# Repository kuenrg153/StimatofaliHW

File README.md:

# StimatofaliHW
Peer-to-Peer Energy

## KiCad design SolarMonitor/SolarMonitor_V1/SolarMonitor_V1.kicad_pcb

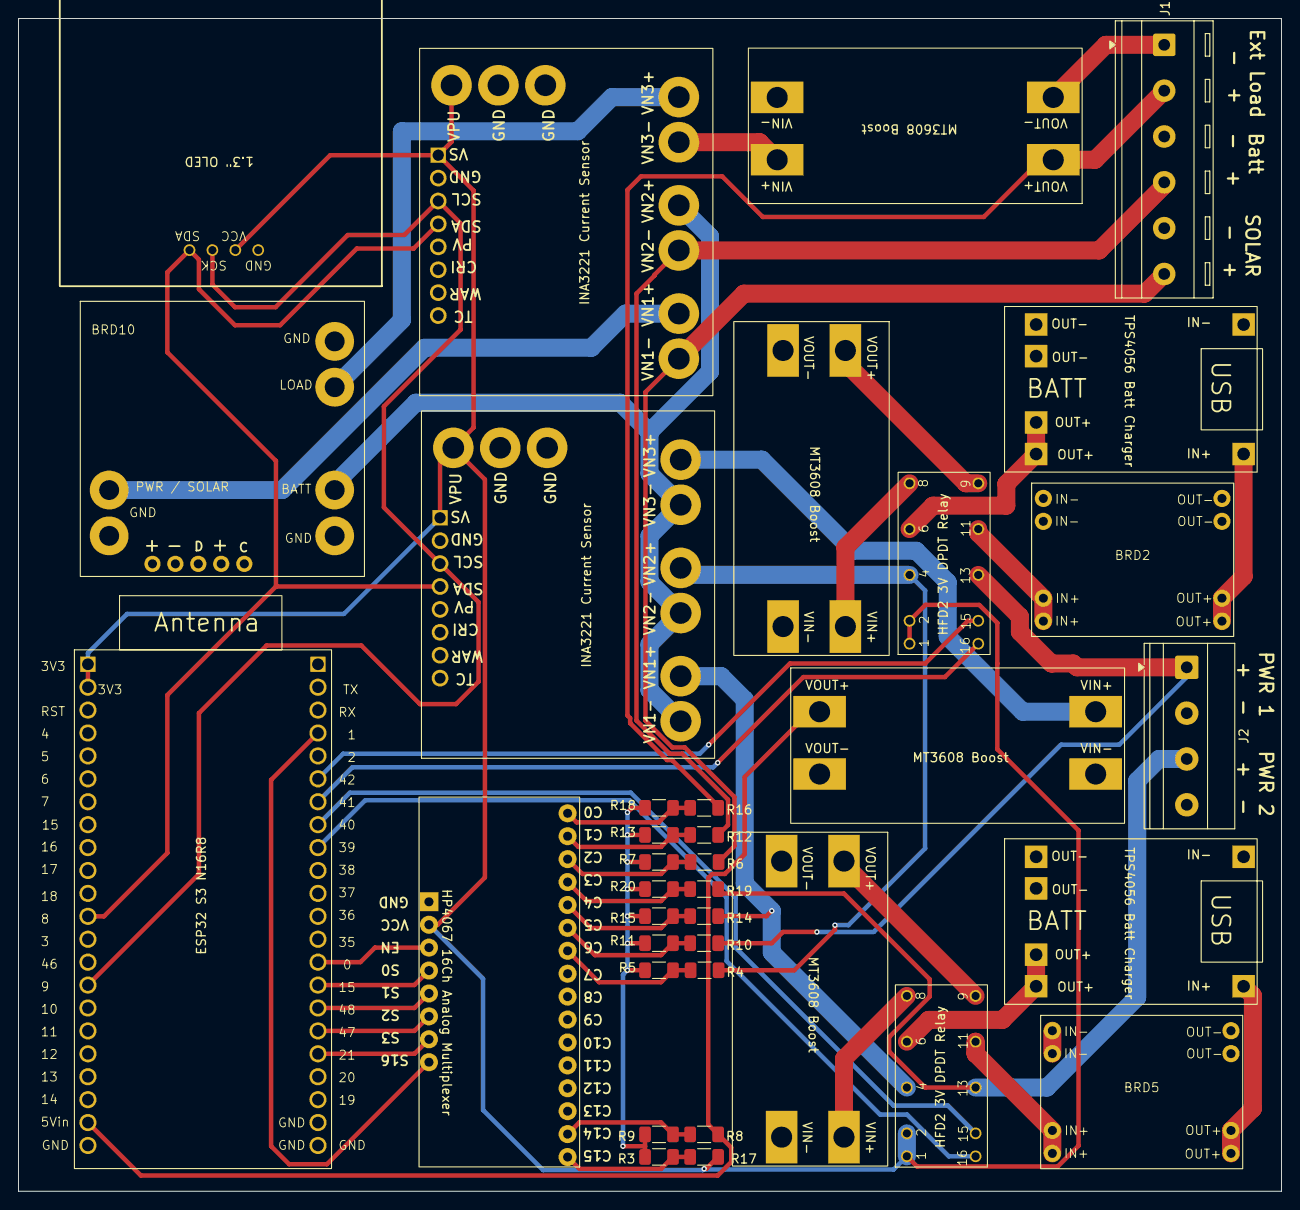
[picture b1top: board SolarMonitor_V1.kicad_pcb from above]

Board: 4 copper layers, 140.0 x 130.0 mm, 36 parts (0 on the bottom side), 46 nets.

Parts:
BRD1, BRD4: TPS4056; TP4056 Battery Charger
BRD2, BRD5: MP1584
BRD3, BRD6, BRD11, BRD14: MT3608; MT3608 Boost
BRD7: HP4067 Analog Multplexer; HP4067 16Ch Analog Multiplexer
BRD8, BRD9: INA3221 Current Sensor
BRD10: MCP73871 Solar Charger; MCP73871
BRD12: ESP32-S3-N16R8
BRD13: 1.3OLED GME12864
J1: Screw_Terminal_01x06; TerminalBlock_RND_205-00291_1x06_P5.08mm_Horizontal
J2: Screw_Terminal_01x04; TerminalBlock_Phoenix_MKDS-1,5-4-5.08_1x04_P5.08mm_Horizont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
K1, K2: HFD2-003-M-L2-D; HFD2 DPDT Relay
R3, R4, R5, R6, R8, R9, R12, R13, R14, R15, R16, R17: 50k; R_1206_3216Metric_Pad1.30x1.75mm_HandSolder
R7, R11, R18, R20: 10k; R_1206_3216Metric_Pad1.30x1.75mm_HandSolder
R10, R19: 100k; R_1206_3216Metric_Pad1.30x1.75mm_HandSolder

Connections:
3V3: BRD7.23 (VCC), BRD8.8 (VS), BRD8.9 (VPU), BRD9.8 (VS), BRD9.9 (VPU), BRD12.1 (3V3), BRD12.2 (3V3), BRD13.2 (VCC), K1.1, K1.2, K2.1, K2.2, R17.1
/5V: BRD11.4 (VOUT+), BRD12.21 (5Vin), R8.1
/AnaVoutMulti: BRD7.17 (S16), BRD12.26 (1)
/Battery+: BRD8.15 (VN2-), J1.4, R12.1
/Conn1Hi: J2.1, K1.13, R10.1
/Conn1Lo: BRD9.14 (VN2+), K1.4, R4.1
/Conn1Reset: BRD12.28 (42), K1.15
/Conn1Set: BRD12.29 (41), K1.16
/Conn2Hi: J2.3, K2.13, R19.1
/Conn2Lo: BRD9.16 (VN1+), K2.4, R14.1
/Conn2Reset: BRD12.30 (40), K2.15
/Conn2Set: BRD12.31 (39), K2.16
/Current Meas & Solar/BattHi: BRD8.14 (VN2+), BRD9.13 (VN3-), BRD9.15 (VN2-), BRD9.17 (VN1-), BRD10.5 (BATT)
/Current Meas & Solar/ExtLoadHi: BRD8.12 (VN3+), BRD10.4 (LOAD)
/Current Meas & Solar/InternalLoad: BRD9.12 (VN3+), BRD11.1 (VIN+)
/Current Meas & Solar/SCL: BRD8.6 (SCL), BRD9.6 (SCL), BRD12.15 (9), BRD13.3 (SCK)
/Current Meas & Solar/SDA: BRD8.5 (SDA), BRD9.5 (SDA), BRD12.12 (8), BRD13.4 (SDA)
/Current Meas & Solar/SolarPanelHi: BRD8.16 (VN1+), BRD10.1 (PWR)
/ExtLoad+: BRD14.4 (VOUT+), J1.2, R16.1
/MultiAdd0: BRD7.21 (S0), BRD12.37 (15)
/MultiAdd1: BRD7.20 (S1), BRD12.38 (48)
/MultiAdd2: BRD7.19 (S2), BRD12.39 (47)
/MultiAdd3: BRD7.18 (S3), BRD12.40 (21)
/MultiEn: BRD7.22 (EN), BRD12.36 (0)
/SolarPanel+: BRD8.17 (VN1-), J1.6, R6.1
GND: BRD1.3 (OUT-), BRD1.4 (OUT-), BRD1.6 (IN-), BRD2.1 (IN-), BRD2.2 (IN-), BRD2.7 (OUT-), BRD2.8 (OUT-), BRD3.2 (VIN-), BRD3.3 (VOUT-), BRD4.3 (OUT-), BRD4.4 (OUT-), BRD4.6 (IN-), BRD5.1 (IN-), BRD5.2 (IN-), BRD5.7 (OUT-), BRD5.8 (OUT-), BRD6.2 (VIN-), BRD6.3 (VOUT-), BRD7.24 (GND), BRD8.7 (GND), BRD8.10 (GND), BRD8.11 (GND), BRD9.7 (GND), BRD9.10 (GND), BRD9.11 (GND), BRD10.2 (GND), BRD10.3 (GND), BRD10.6 (GND), BRD11.2 (VIN-), BRD11.3 (VOUT-), BRD12.22 (GND), BRD12.23 (GND), BRD12.43 (GND), BRD12.44 (GND), BRD13.1 (GND), BRD14.2 (VIN-), BRD14.3 (VOUT-), J1.1, J1.3, J1.5, J2.2, J2.4, R3.2, R5.2, R7.2, R9.2, R11.2, R13.2, R15.2, R18.2, R20.2
unnamed: BRD1.5 (IN+), BRD2.5 (OUT+), BRD2.6 (OUT+)
unnamed: BRD1.1 (OUT+), BRD1.2 (OUT+), K1.6
unnamed: BRD2.3 (IN+), BRD2.4 (IN+), K1.11
unnamed: BRD3.1 (VIN+), K1.8
unnamed: BRD3.4 (VOUT+), K1.9
unnamed: BRD4.5 (IN+), BRD5.5 (OUT+), BRD5.6 (OUT+)
unnamed: BRD4.1 (OUT+), BRD4.2 (OUT+), K2.6
unnamed: BRD5.3 (IN+), BRD5.4 (IN+), K2.11
unnamed: BRD6.1 (VIN+), K2.8
unnamed: BRD6.4 (VOUT+), K2.9
unnamed: BRD7.16 (C0), R16.2, R18.1
unnamed: BRD7.15 (C1), R12.2, R13.1
unnamed: BRD7.14 (C2), R6.2, R7.1
unnamed: BRD7.13 (C3), R19.2, R20.1
unnamed: BRD7.12 (C4), R14.2, R15.1
unnamed: BRD7.11 (C5), R10.2, R11.1
unnamed: BRD7.10 (C6), R4.2, R5.1
unnamed: BRD7.2 (C14), R8.2, R9.1
unnamed: BRD7.1 (C15), R3.1, R17.2
unnamed: BRD8.13 (VN3-), BRD14.1 (VIN+)

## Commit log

2025-08-14 V0.1
    Needs layout
2025-08-16 First Push
2025-10-01 V1 As ordered
